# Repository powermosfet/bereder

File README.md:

# bereder
Over-engineered outage-alarm for the water heater

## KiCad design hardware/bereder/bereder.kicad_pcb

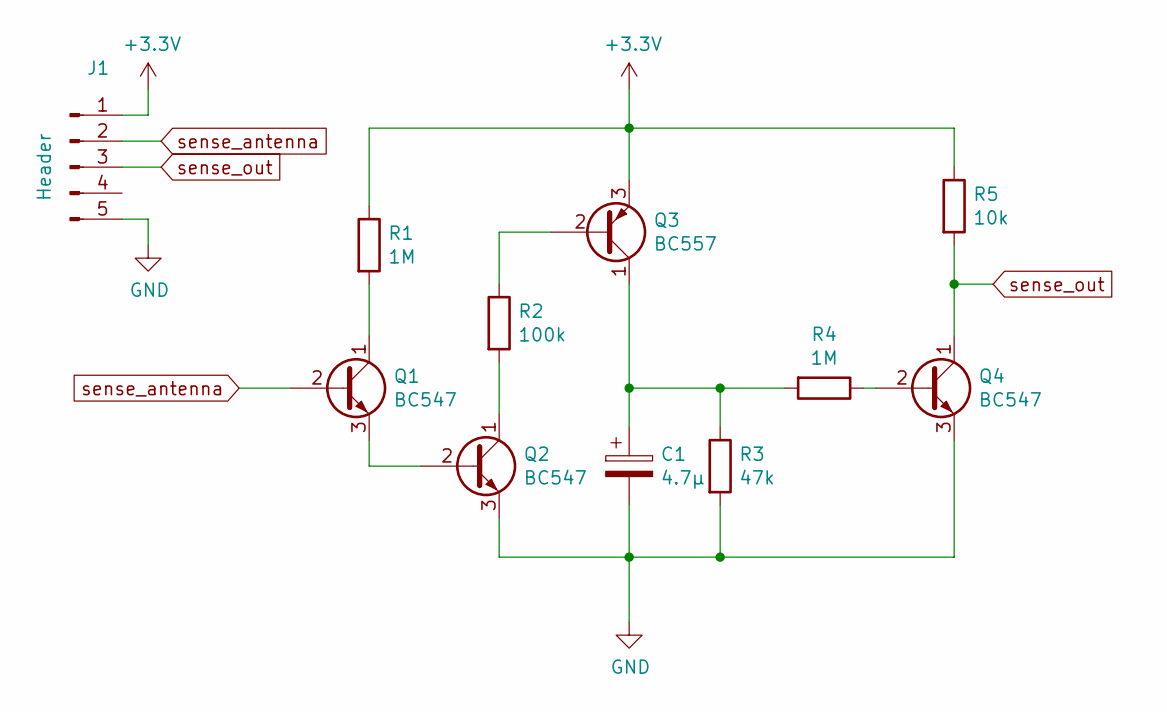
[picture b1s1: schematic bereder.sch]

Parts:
C1: 4.7µ; CP_Radial_D5.0mm_P2.50mm
J1: Header; PinHeader_1x05_P1.00mm_Vertical
Q1, Q2, Q4: BC547; TO-92_Inline
Q3: BC557; TO-92_Inline
R1, R4: 1M; R_Axial_DIN0207_L6.3mm_D2.5mm_P2.54mm_Vertical
R2: 100k; R_Axial_DIN0207_L6.3mm_D2.5mm_P2.54mm_Vertical
R3: 47k; R_Axial_DIN0207_L6.3mm_D2.5mm_P2.54mm_Vertical
R5: 10k; R_Axial_DIN0207_L6.3mm_D2.5mm_P2.54mm_Vertical

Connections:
+3V3: J1.1, Q3.3 (E), R1.1, R5.1
GND: C1.2, J1.5, Q2.3 (E), Q4.3 (E), R3.2
unnamed: C1.1, Q3.1 (C), R3.1, R4.2
unnamed: Q1.1 (C), R1.2
unnamed: Q1.3 (E), Q2.2 (B)
unnamed: Q2.1 (C), R2.2
unnamed: Q3.2 (B), R2.1
unnamed: Q4.2 (B), R4.1
sense_antenna: J1.2, Q1.2 (B)
sense_out: J1.3, Q4.1 (C), R5.2

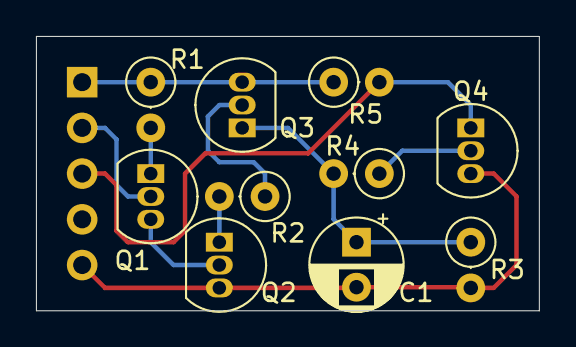
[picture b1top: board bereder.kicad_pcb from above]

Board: 2 copper layers, 27.9 x 15.2 mm, 11 parts (1 on the bottom side), 10 nets.

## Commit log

2021-04-01 Fix nix deps
